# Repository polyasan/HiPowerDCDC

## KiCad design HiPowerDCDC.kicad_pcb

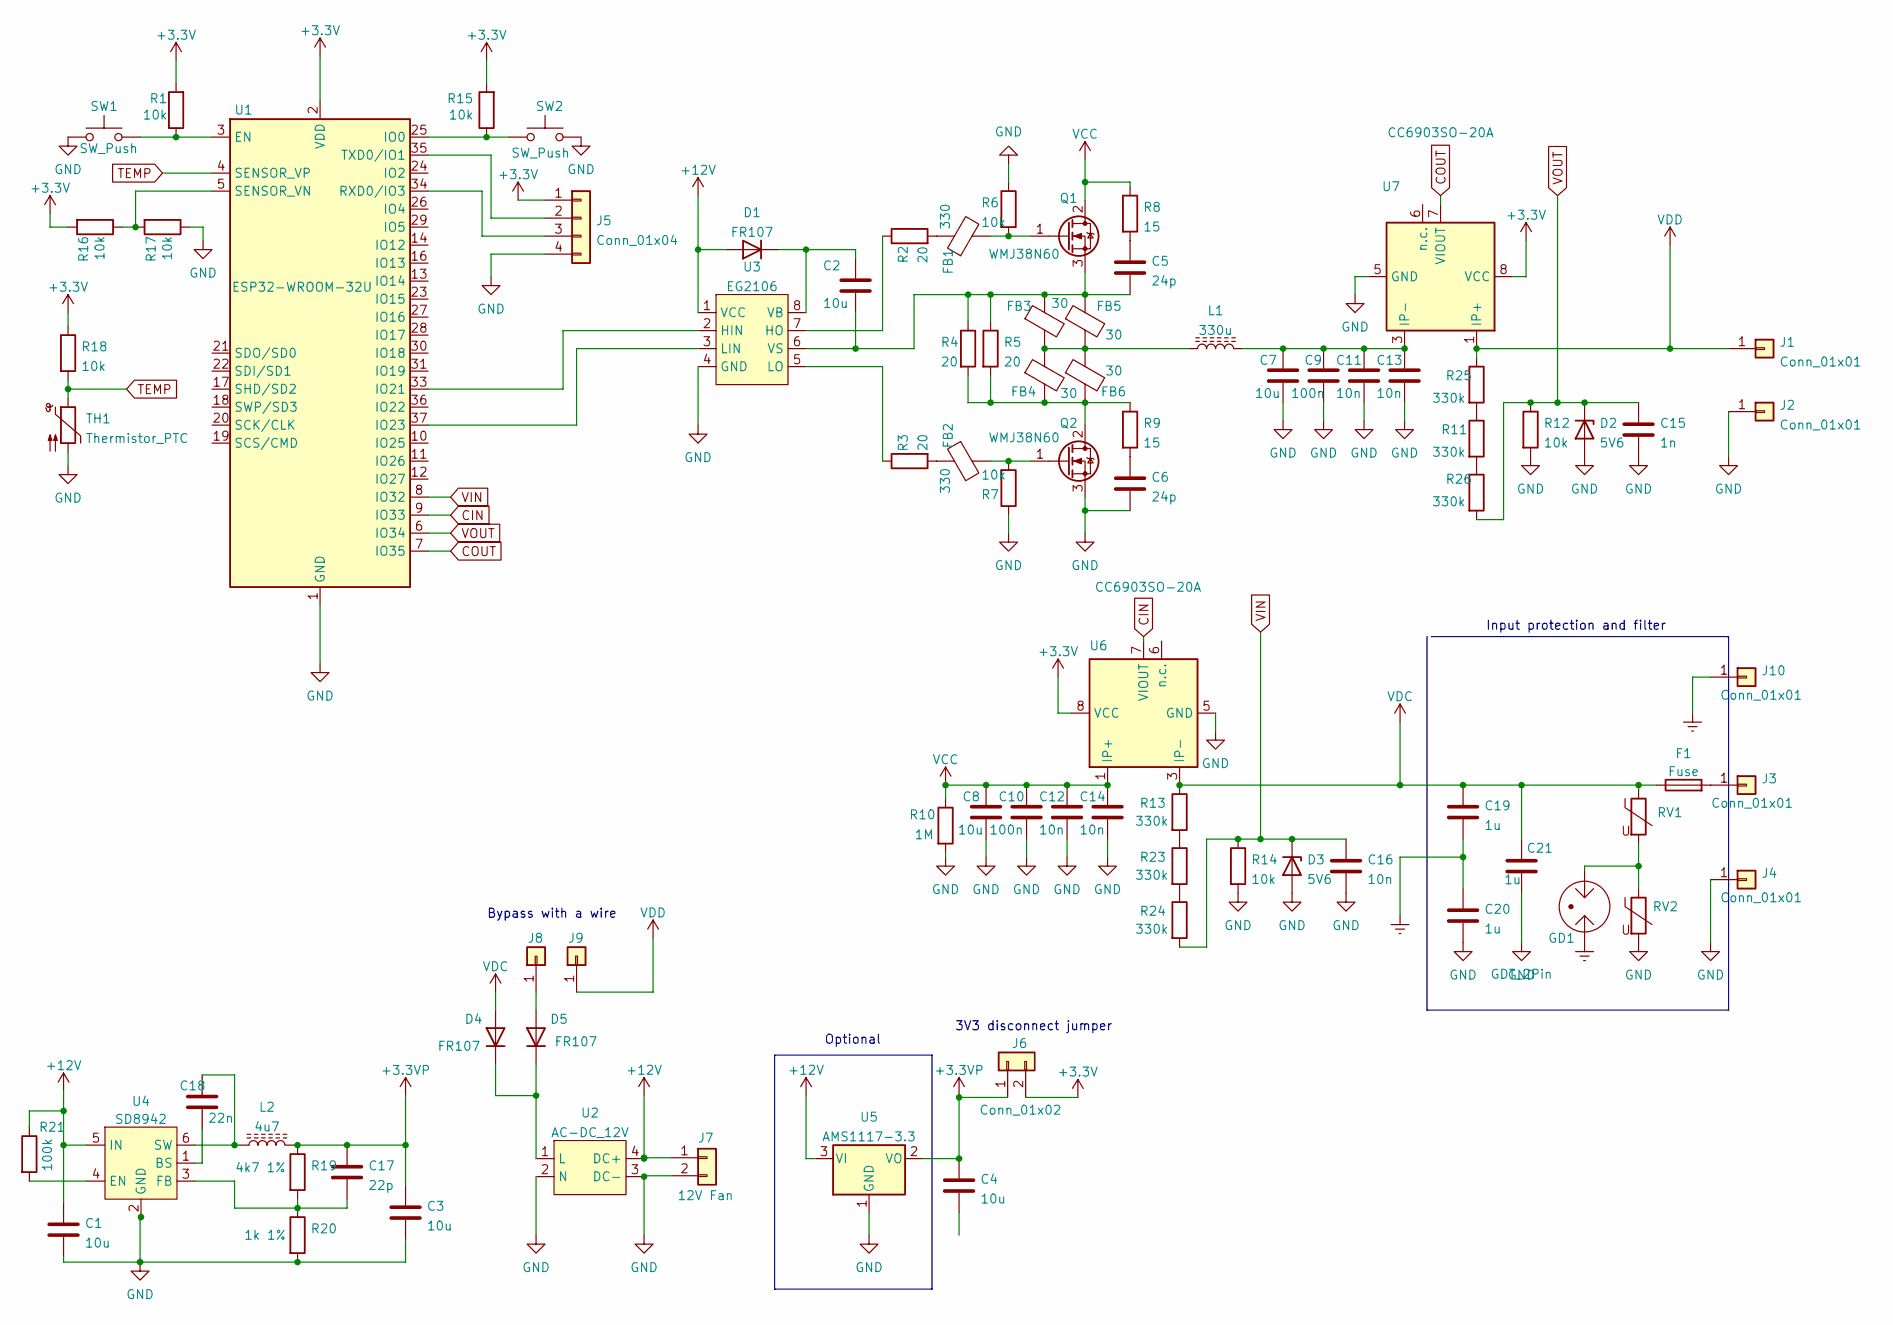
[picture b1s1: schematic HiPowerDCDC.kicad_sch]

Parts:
C1, C2, C3, C4: 10u; C_1206_3216Metric
C5, C6: 24p; C_1206_3216Metric
C7, C8: 10u; CP_Rect_L42.0mm_T20.0mm_H40.0mm
C9, C10: 100n; C_1812_4532Metric
C11, C12, C13, C14: 10n; C_1812_4532Metric
C15: 1n; C_1206_3216Metric
C16: 10n; C_1206_3216Metric
C17: 22p; C_1206_3216Metric
C18: 22n; C_1206_3216Metric
C19, C20, C21: 1u; C_Rect_L26.5mm_W11.5mm_P22.50mm_MKS4
D1, D4, D5: FR107; D_SOD-123
D2, D3: 5V6; D_1206_3216Metric
F1: Fuse; Fuseholder_Schurter_0751.0505
FB1, FB2: 330; L_1206_3216Metric
FB3, FB4, FB5, FB6: 30; L_1206_3216Metric
GD1: GDT_2Pin; CG2-350L
J1, J2, J3, J4, J10: Conn_01x01; Keystone_7808
J5: Conn_01x04; PinHeader_1x04_P2.54mm_Vertical
J6: Conn_01x02; PinHeader_1x02_P2.54mm_Vertical
J7: 12V Fan; PinHeader_1x02_P2.54mm_Vertical
J8, J9: VDD_BP; PinSocket_1x01_P2.54mm_Vertical
L1: 330u; L_Toroid_Vertical_L54.0mm_W23.8mm_P20.10mm_Bourns_5700
L2: 4u7; L_1210_3225Metric
Q1, Q2: WMJ38N60; TO-247-3_Vertical
R1, R6, R7, R12, R14, R15, R16, R17, R18: 10k; R_1206_3216Metric
R2, R3, R4, R5: 20; R_1206_3216Metric
R8, R9: 15; R_1206_3216Metric
R10: 1M; R_Axial_DIN0207_L6.3mm_D2.5mm_P10.16mm_Horizontal
R11, R13, R23, R24, R25, R26: 330k; R_1206_3216Metric
R19: 4k7 1%; R_1206_3216Metric
R20: 1k 1%; R_1206_3216Metric
R21: 100k; R_1206_3216Metric
RV1, RV2: V275LA20AP; RV_Disc_D15.5mm_W3.9mm_P7.5mm
SW1, SW2: SW_Push; SW_Push_1P1T_NO_6x6mm_H9.5mm
TH1: Thermistor_PTC; PinHeader_1x02_P2.54mm_Vertical
U1: ESP32-WROOM-32U; ESP32-WROOM-32
U2: AC-DC_12V; HLK-PM12
U3: EG2106; SO-8_3.9x4.9mm_P1.27mm
U4: SD8942; SOT-23-6
U5: AMS1117-3.3; SOT-223-3_TabPin2
U6, U7: CC6903SO-20A; SO-8_3.9x4.9mm_P1.27mm

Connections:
+3.3VP: C3.1, C4.1, C17.1, J6.1, L2.2, R19.1, U5.2 (VO)
+3V3: J5.1, J6.2, R1.2, R15.2, R16.2, R18.1, U1.2 (VDD), U6.8 (VCC), U7.8 (VCC)
+12V: C1.1, D1.2 (A), J7.1, R21.1, U2.4 (DC+), U3.1 (VCC), U4.5 (IN), U5.3 (VI)
CIN: U1.9 (IO33), U6.7 (VIOUT)
COUT: U1.7 (IO35), U7.7 (VIOUT)
Earth: C19.2, C20.1, GD1.1, J10.1
GND: C1.2, C3.2, C6.2, C7.2, C8.2, C9.2, C10.2, C11.2, C12.2, C13.2, C14.2, C15.2, C16.2, C20.2, C21.2, D2.2 (A), D3.2 (A), J2.1, J4.1, J5.4, J7.2, Q2.3 (S), R6.1, R7.1, R10.2, R12.2, R14.2, R17.1, R20.2, RV2.2, SW1.1, SW2.2, TH1.2, U1.1 (GND), U1.15 (GND), U1.38 (GND), U1.39 (GND), U2.2 (N), U2.3 (DC-), U3.4 (GND), U5.1 (GND), U6.5 (GND), U7.5 (GND)
unnamed: C2.1, C5.2, FB3.1, FB5.1, Q1.3 (S), R4.1, R5.1, U3.6 (VS)
unnamed: C2.2, D1.1 (K), U3.8 (VB)
unnamed: C5.1, R8.2
unnamed: C6.1, R9.2
unnamed: C7.1, C9.1, C11.1, C13.1, L1.2, U7.3 (IP-), U7.4 (IP-)
unnamed: C17.2, R19.2, R20.1, U4.3 (FB)
unnamed: C18.1, L2.1, U4.6 (SW)
unnamed: C18.2, U4.1 (BS)
unnamed: D4.1 (K), D5.1 (K), U2.1 (L)
unnamed: D5.2 (A), J8.1
unnamed: F1.2, J3.1
unnamed: FB1.1, R2.2
unnamed: FB1.2, Q1.1 (G), R6.2
unnamed: FB2.1, R3.2
unnamed: FB2.2, Q2.1 (G), R7.2
unnamed: FB3.2, FB4.1, FB5.2, FB6.1, L1.1
unnamed: FB4.2, FB6.2, Q2.2 (D), R4.2, R5.2, R9.1
unnamed: GD1.2, RV1.2, RV2.1
unnamed: J5.2, U1.35 (TXD0/IO1)
unnamed: J5.3, U1.34 (RXD0/IO3)
unnamed: R1.1, SW1.2, U1.3 (EN)
unnamed: R2.1, U3.7 (HO)
unnamed: R3.1, U3.5 (LO)
unnamed: R11.1, R25.2
unnamed: R11.2, R26.1
unnamed: R13.2, R23.1
unnamed: R15.1, SW2.1, U1.25 (IO0)
unnamed: R16.1, R17.2, U1.5 (SENSOR_VN)
unnamed: R21.2, U4.4 (EN)
unnamed: R23.2, R24.1
unnamed: U1.33 (IO21), U3.2 (HIN)
unnamed: U1.37 (IO23), U3.3 (LIN)
TEMP: R18.2, TH1.1, U1.4 (SENSOR_VP)
VCC: C8.1, C10.1, C12.1, C14.1, Q1.2 (D), R8.1, R10.1, U6.1 (IP+), U6.2 (IP+)
VDC: C19.1, C21.1, D4.2 (A), F1.1, R13.1, RV1.1, U6.3 (IP-), U6.4 (IP-)
VDD: J1.1, J9.1, R25.1, U7.1 (IP+), U7.2 (IP+)
VIN: C16.1, D3.1 (K), R14.1, R24.2, U1.8 (IO32)
VOUT: C15.1, D2.1 (K), R12.1, R26.2, U1.6 (IO34)

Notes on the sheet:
3V3 disconnect jumper
Optional
Bypass with a wire
Input protection and filter

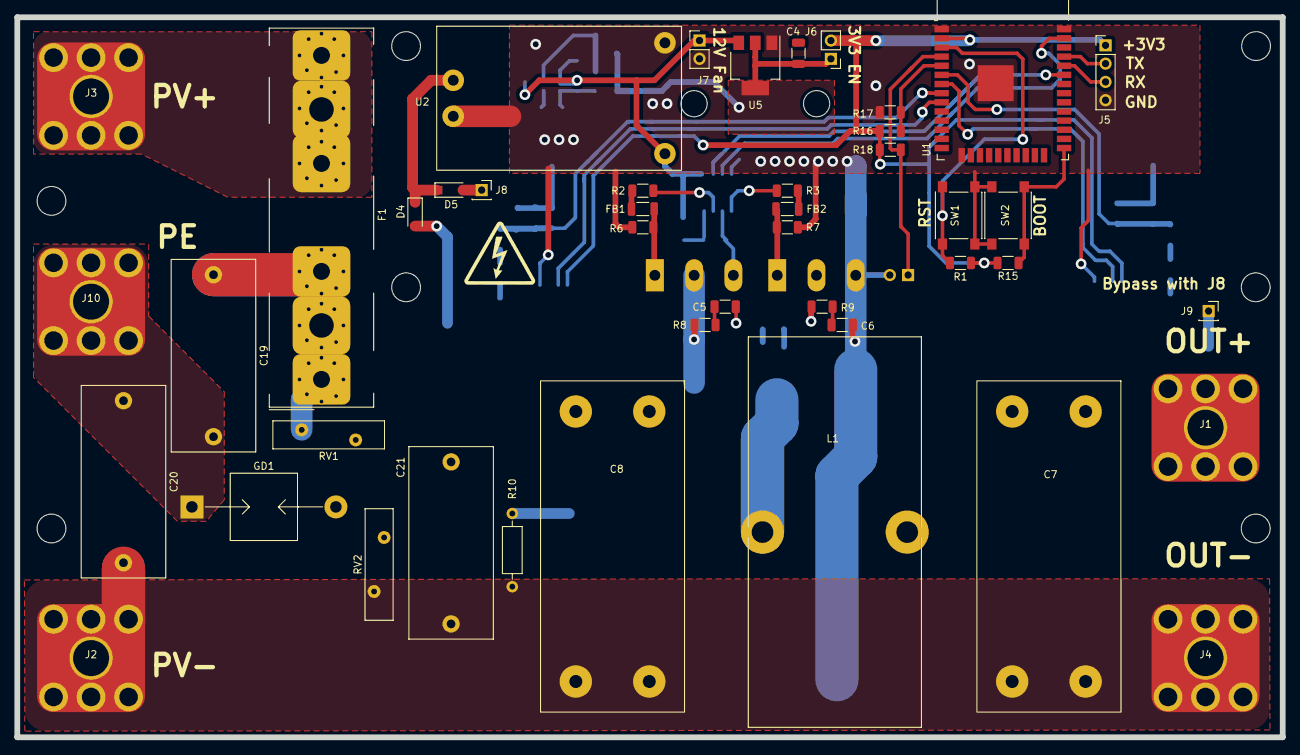
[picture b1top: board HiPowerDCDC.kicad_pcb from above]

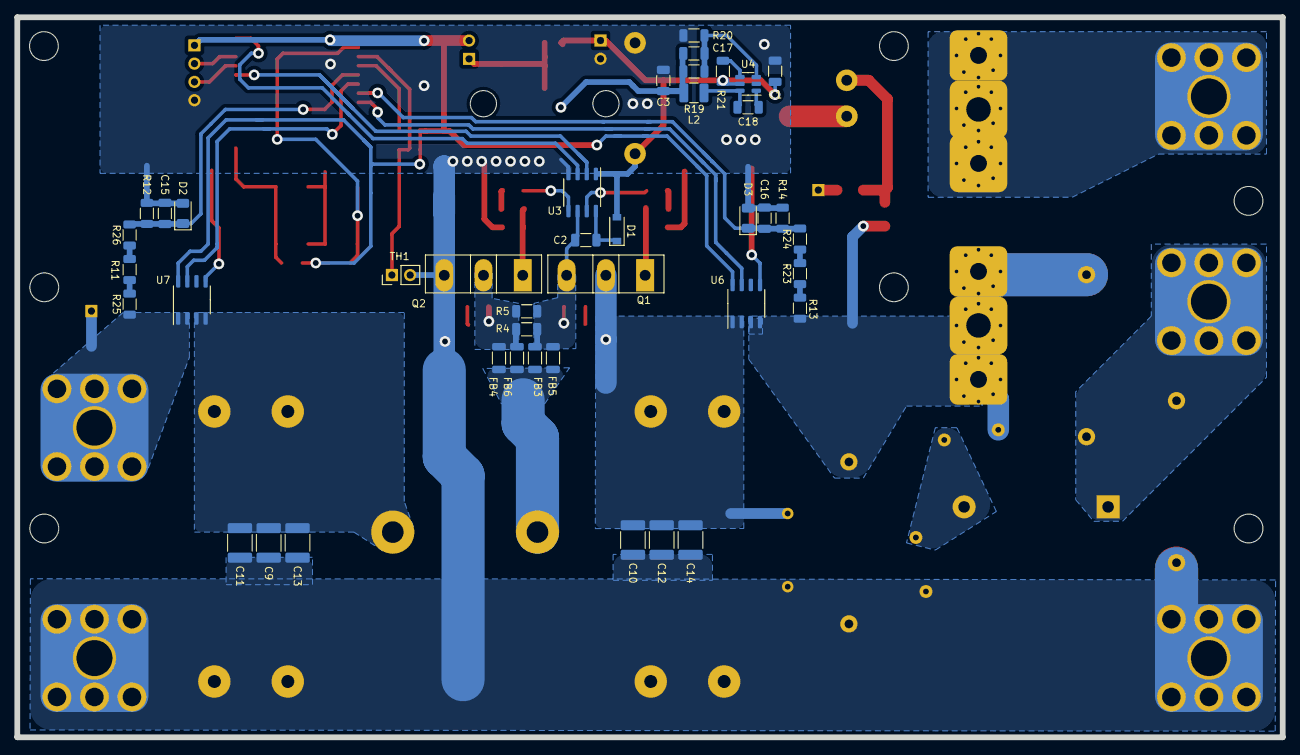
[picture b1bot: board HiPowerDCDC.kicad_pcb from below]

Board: 2 copper layers, 175.8 x 100.0 mm, 85 parts (41 on the bottom side), 45 nets.

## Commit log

2022-04-19 Uploaded project files
2022-04-19 Modified via size
2022-04-19 Created lead filled channels on high current tracks
2022-04-19 Small modifications
2022-04-19 Modified HV tracks and cleaned up PCB
2022-04-19 Added ACDC 3d model, reorganized switching FETs
2022-04-19 Placed mounting holes
2022-04-19 Changed to high voltage capacitors
2022-04-19 Laci, check this out
2022-04-20 Added PTC sensor, Laci you didn't check me :(
2022-04-20 Added Keystone connectors
2022-04-20 Added 3d models
2022-04-21 Changed FR107 footprint
2022-04-21 Increased PCB width and made high P component more spaceous
2022-04-21 Added DCDC converter 12V->5V
2022-04-21 Changed ACDC converter to HLK-PM12
2022-04-21 Finished PCB
2022-04-22 Changed ACS770 to CC6900
2022-04-22 Added logos and 3V3 enable pin
2022-04-22 Added fan output and changed XT3410 to SD8942
2022-04-22 Increased DCDC inductor footprint
2022-04-22 Finished PCB..then Laci started to complain :(
2022-04-22 Laci, do you want me to re design the whole f*kin PCB?
2022-04-23 Finalized PCB
2022-04-29 Added FW and fixed monor bugs
2022-05-02 Created basic FW
